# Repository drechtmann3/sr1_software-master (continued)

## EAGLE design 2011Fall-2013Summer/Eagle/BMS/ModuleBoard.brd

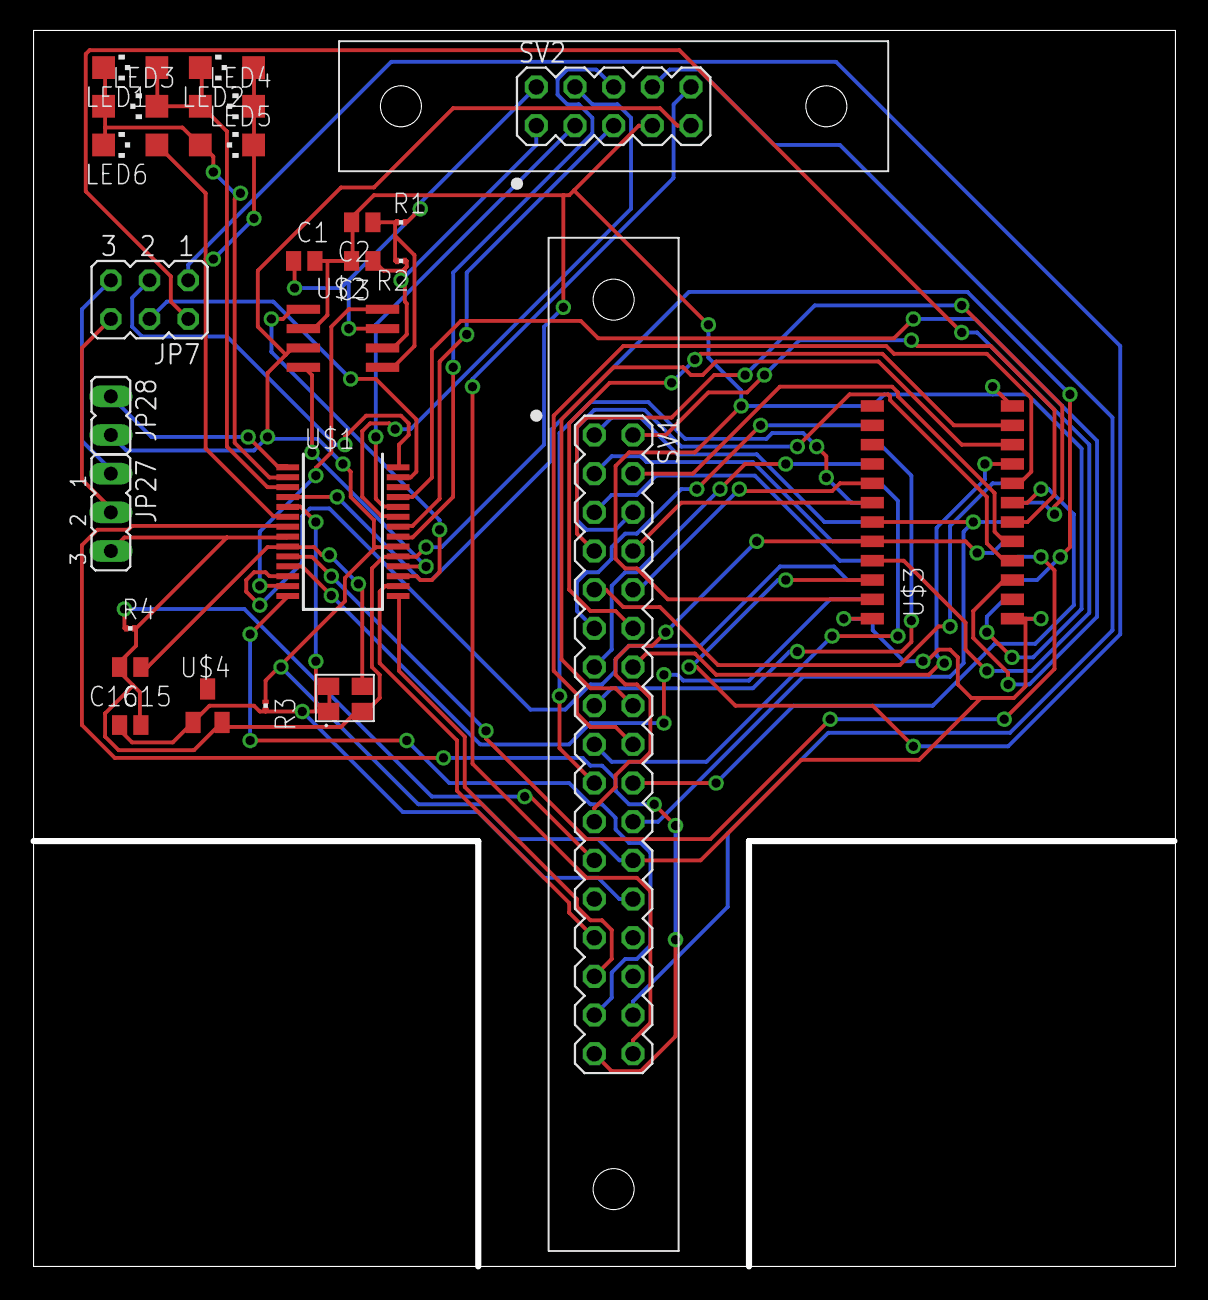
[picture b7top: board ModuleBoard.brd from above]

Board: 2 copper layers, 75.0 x 81.2 mm, 26 parts (1 on the bottom side), 58 nets.

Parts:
C1, C3: 100pF; C0504
C2: 47nF; C0504
C15: 10nF; C0504
C16: 15pF; C0504
JP7: JP3Q
JP27: JP2
JP28: JP1
LED1, LED2, LED3, LED4, LED5, LED6: CHIPLED_1206
R1, R2: 1k3; R0201
R3: 150; R0201
R4: 0; R0201
SV1: MA17-2
SV2: AMP_LATCH_10; MA05-2
U$1: PIC18F23K22; SSOP28
U$2: TJA1040; SO-08
U$3, U$5: CD4514BM96E4; SOIC-24
U$4: LM4040; SOT23
U$11: CTS632

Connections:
12V+: SV1.34, SV2.10
12V-: SV1.32, SV2.8
AGND_PLANE: R4.1, SV1.23
CAN: U$1.13, U$2.8
CANH: C1.1, R1.2, SV2.2, U$2.7
CANL: C3.1, R2.1, SV2.1, U$2.6
CLK: SV1.31, U$1.14
CS: SV1.33, U$1.7
DIN: SV1.29, U$1.15
DOUT: SV1.27, U$1.16
GND: C1.2, C2.2, C3.2, C15.2, C16.2, JP27.3, R4.2, SV2.7, U$1.8, U$1.19, U$2.2, U$3.12, U$3.23, U$4.2, U$5.12, U$5.23, U$11.2
I2C_CS: SV2.6, U$1.21
I2C_SCL: SV2.5, U$1.22
I2C_SDI: SV2.4, U$1.23
I2C_SDO: SV2.3, U$1.24
unnamed: LED1.A, LED2.C, LED3.C, LED4.A, U$1.3
unnamed: U$1.4, U$5.22
unnamed: U$1.10, U$5.21
unnamed: U$1.11, U$5.2
unnamed: U$1.18, U$2.4
unnamed: U$1.12, U$5.3
unnamed: LED1.C, LED3.A, LED5.A, LED6.C, U$1.2
unnamed: LED2.A, LED4.C, LED5.C, LED6.A, U$1.6
unnamed: U$1.17, U$2.1
unnamed: JP28.1, U$1.1
unnamed: JP7.5, JP27.1
unnamed: JP7.6, JP27.2
unnamed: U$1.25, U$3.3
unnamed: JP7.1, U$3.22
unnamed: JP7.2, U$3.21
unnamed: C2.1, R1.1, R2.2, U$2.5
unnamed: C16.1, U$1.9, U$11.3
PGC: JP7.4, U$1.27
PGD: JP7.3, U$1.28
RELAYA: SV1.21, U$3.20, U$5.20
RELAYB: SV1.22, U$3.19, U$5.19
VDD_PLANE: JP28.2, R3.1, SV1.24, SV2.9, U$1.20, U$2.3, U$3.1, U$3.24, U$5.1, U$5.24
VREF: C15.1, R3.2, SV1.26, U$1.5, U$4.1, U$11.1, U$11.4
X0A: SV1.1, U$5.6
X0B: SV1.2, U$3.6
X1A: SV1.3, U$5.5
X1B: SV1.4, U$3.5
X2A: SV1.5, U$5.4
X2B: SV1.6, U$3.4
X3A: SV1.7, U$5.18
X3B: SV1.8, U$3.18
X4A: SV1.9, U$5.17
X4B: SV1.10, U$3.17
Y0A: SV1.11, U$5.11
Y0B: SV1.12, U$3.11
Y1A: SV1.13, U$5.9
Y1B: SV1.14, U$3.9
Y2A: SV1.15, U$5.10
Y2B: SV1.16, U$3.10
Y3A: SV1.17, U$5.8
Y3B: SV1.18, U$3.8
Y4A: SV1.19, U$5.7
Y4B: SV1.20, U$3.7
